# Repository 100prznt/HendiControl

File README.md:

# HendiControl

## Konzept

## Remote Controller

PCB vom ersten Prototypen auf Basis WeMos D1 mini

## Reverse engineering

### PCB Display

Vorderseite *BETTER BT-350Q_DIS(V05) SH13383 15.10.22*

Rückseite

Der auf der Rückseite verbaute IC trägt die Bezeichnung __SM1628__. Nach einer ersten Rechereche handelt es sich dabei um einen LED Displaycontroller.
* [Datenblatt SM1628](docu/SM1628.PDF)

### PCB Poti

Vorderseite *HT-1P75*

Rückseite *BETTER*

Verbaut ist ein 500K Poti

### Schaltplan

* [Schaltplan Display u. Poti](reverse_engineering/Schematic_UI.pdf)

| U [V] | P [W] |
|-------|-------|
| 0     | 3500  |
| 5     | 500   |

### Nützliche Links

* [craftbeerpi Wiki - Hendi-Induction-cooker-model-3500-M--Setup](https://github.com/Manuel83/craftbeerpi/wiki/Hendi-Induction-cooker-model-3500-M--Setup)

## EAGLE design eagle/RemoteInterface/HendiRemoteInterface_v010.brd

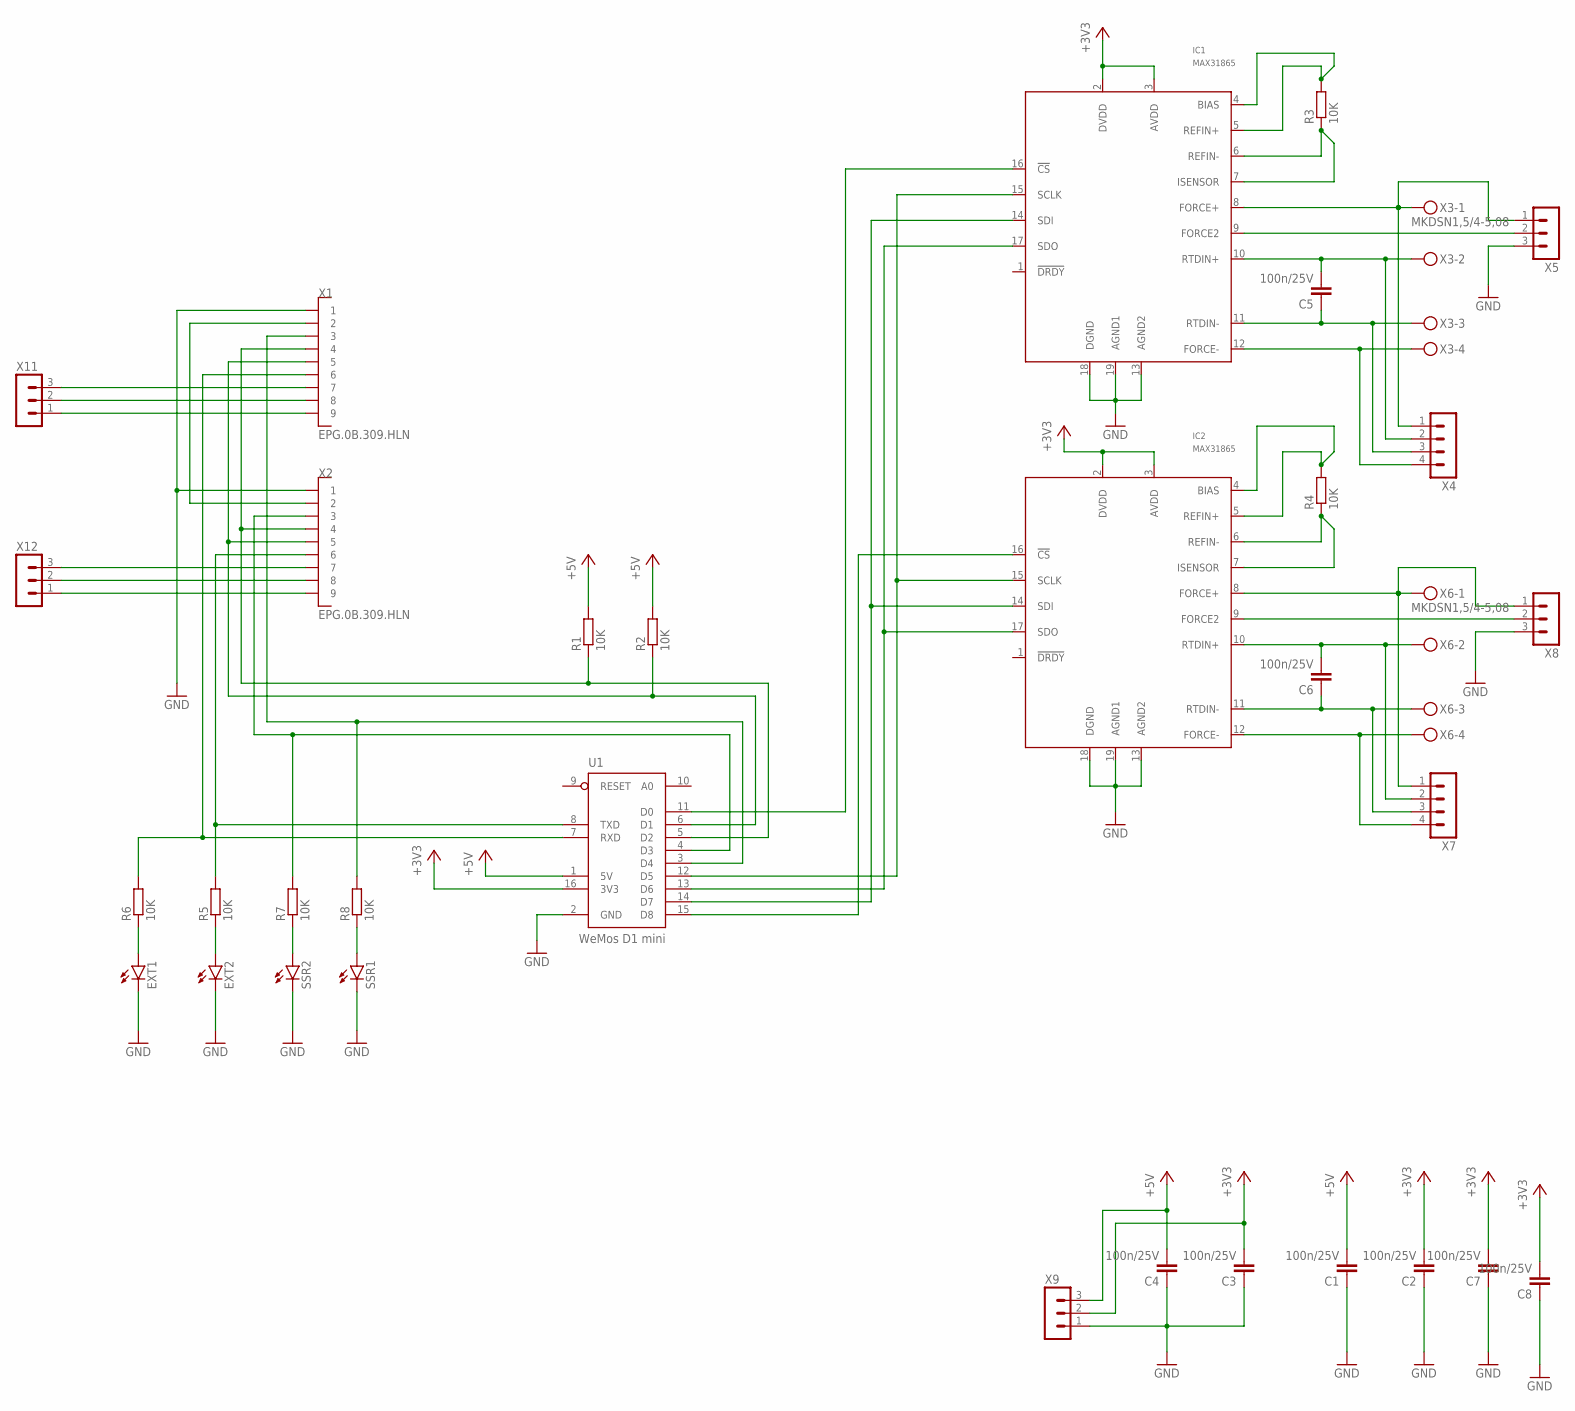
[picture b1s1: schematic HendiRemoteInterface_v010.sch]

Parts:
C1, C2, C3, C4, C5, C6, C7, C8: 100n/25V; C0805
EXT1, EXT2: LEDCHIP-LED0805; CHIP-LED0805
IC1, IC2: MAX31865; SSOP20
R1, R2, R3, R4, R5, R6, R7, R8: 10K; R0805
SSR1, SSR2: LEDCHIP-LED0805; CHIP-LED0805
U1: WeMos D1 mini; D1_MINI
X1, X2: EPG.0B.309.HLN; P19-EPG-EXG-0B.309
X3, X6: MKDSN1,5/4-5,08
X4, X7: MA04-1
X5, X8, X9, X11, X12: MA03-1

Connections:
+3V3: C2.2, C3.2, C7.2, C8.2, IC1.2 (DVDD), IC1.3 (AVDD), IC2.2 (DVDD), IC2.3 (AVDD), U1.16 (3V3), X9.2
+5V: C1.2, C4.2, R1.2, R2.2, U1.1 (5V), X9.3
CLK: IC1.15 (SCLK), IC2.15 (SCLK), U1.12 (D5)
CS1: IC1.16 (!CS), U1.11 (D0)
CS2: IC2.16 (!CS), U1.15 (D8)
GND: C1.1, C2.1, C3.1, C4.1, C7.1, C8.1, EXT1.C, EXT2.C, IC1.13 (AGND2), IC1.18 (DGND), IC1.19 (AGND1), IC2.13 (AGND2), IC2.18 (DGND), IC2.19 (AGND1), SSR1.C, SSR2.C, U1.2 (GND), X1.1, X1.A (GND), X1.B (GND), X1.C (GND), X1.D (GND), X2.1, X2.A (GND), X2.B (GND), X2.C (GND), X2.D (GND), X5.3, X8.3, X9.1
unnamed: X1.8, X11.2
unnamed: X1.7, X11.3
unnamed: X1.9, X11.1
unnamed: R2.1, U1.6 (D1), X1.5, X2.5
unnamed: X1.2, X2.2
unnamed: X2.7, X12.3
unnamed: X2.8, X12.2
unnamed: X2.9, X12.1
unnamed: EXT2.A, R5.1
unnamed: EXT1.A, R6.1
unnamed: R1.1, U1.5 (D2), X1.4, X2.4
unnamed: R7.2, U1.4 (D3), X2.3
unnamed: R8.2, U1.3 (D4), X1.3
unnamed: R5.2, U1.8 (TXD), X2.6
unnamed: R6.2, U1.7 (RXD), X1.6
unnamed: IC2.8 (FORCE+), X6.1, X7.1, X8.1
unnamed: C6.2, IC2.10 (RTDIN+), X6.2, X7.2
unnamed: C6.1, IC2.11 (RTDIN-), X6.3, X7.3
unnamed: IC2.12 (FORCE-), X6.4, X7.4
unnamed: IC1.8 (FORCE+), X3.1, X4.1, X5.1
unnamed: C5.2, IC1.10 (RTDIN+), X3.2, X4.2
unnamed: C5.1, IC1.11 (RTDIN-), X3.3, X4.3
unnamed: IC1.12 (FORCE-), X3.4, X4.4
unnamed: IC1.9 (FORCE2), X5.2
unnamed: IC2.9 (FORCE2), X8.2
unnamed: IC1.6 (REFIN-), IC1.7 (ISENSOR), R3.1
unnamed: IC1.4 (BIAS), IC1.5 (REFIN+), R3.2
unnamed: IC2.6 (REFIN-), IC2.7 (ISENSOR), R4.1
unnamed: IC2.4 (BIAS), IC2.5 (REFIN+), R4.2
unnamed: R7.1, SSR2.A
unnamed: R8.1, SSR1.A
SDI: IC1.14 (SDI), IC2.14 (SDI), U1.14 (D7)
SDO: IC1.17 (SDO), IC2.17 (SDO), U1.13 (D6)

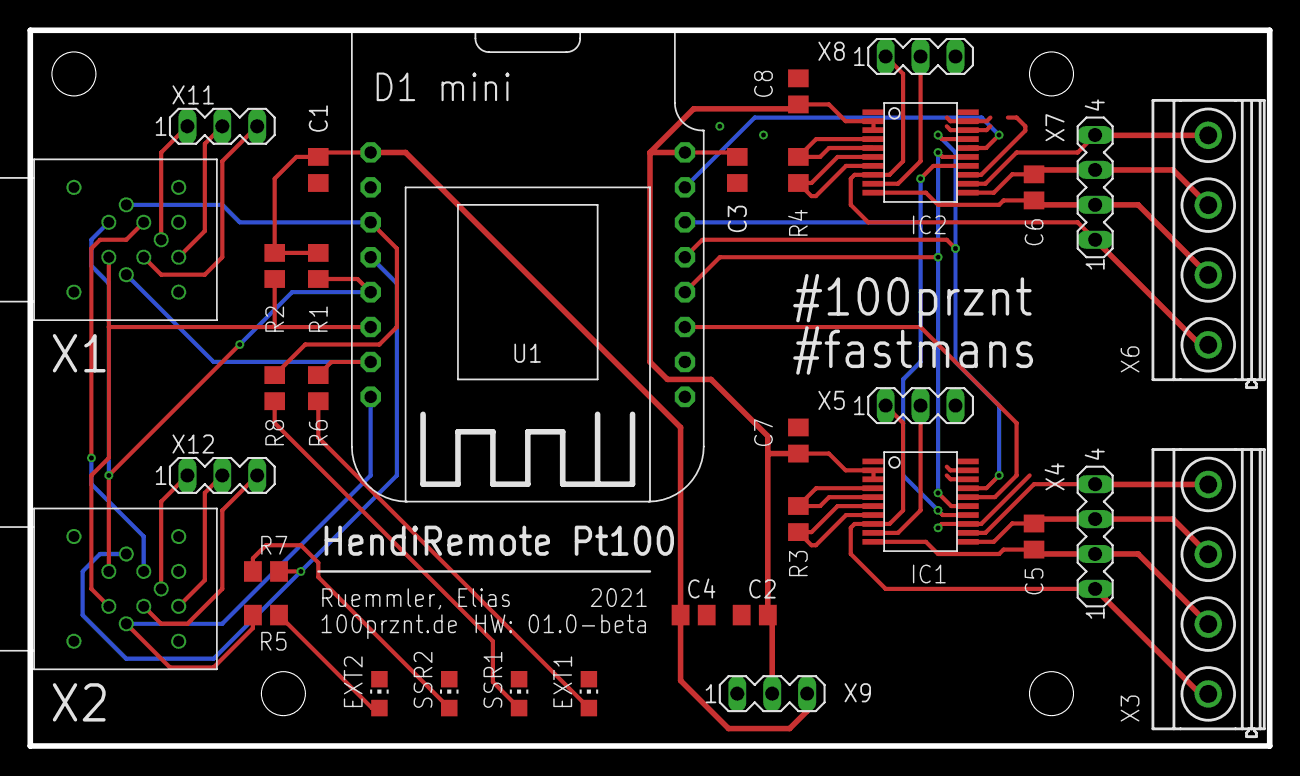
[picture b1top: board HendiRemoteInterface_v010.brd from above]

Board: 2 copper layers, 90.2 x 52.1 mm, 34 parts (0 on the bottom side), 39 nets.

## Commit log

2021-01-28 add docu and photos
2021-01-28 Add schematics
2021-01-28 Add PCB markings
2021-02-17 Add small photos
2021-02-26 Add HendiRemote Eagle Project
2021-03-01 add hendiremote
